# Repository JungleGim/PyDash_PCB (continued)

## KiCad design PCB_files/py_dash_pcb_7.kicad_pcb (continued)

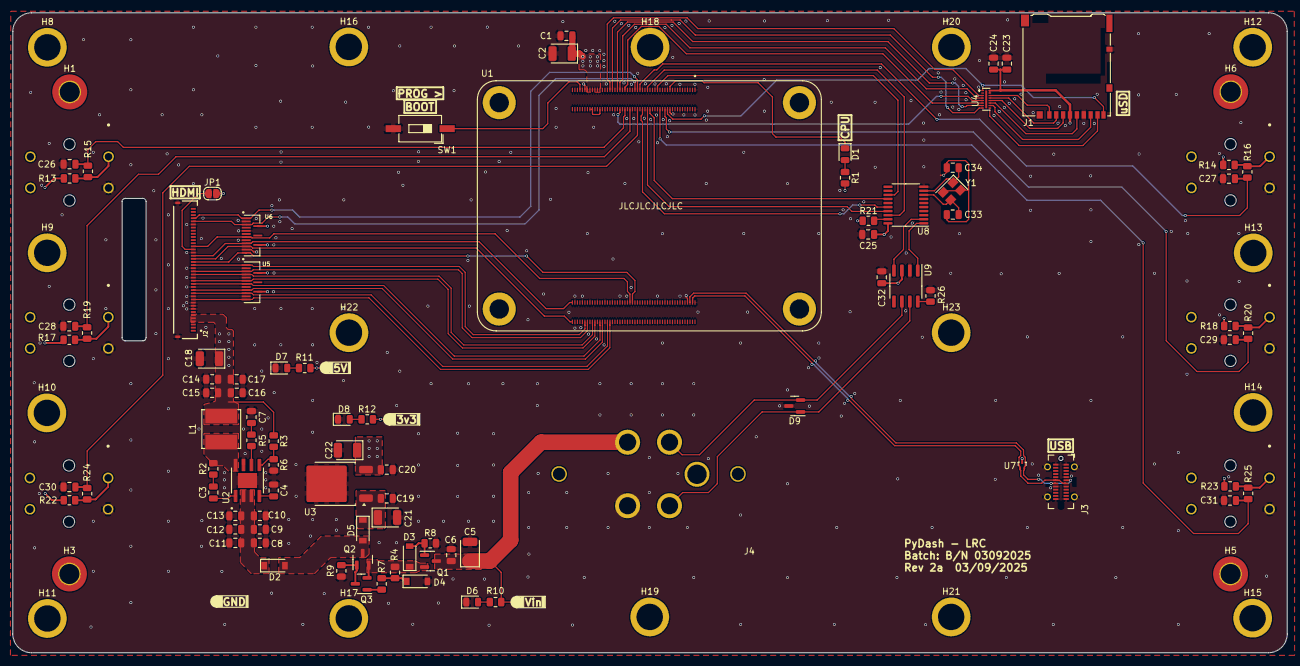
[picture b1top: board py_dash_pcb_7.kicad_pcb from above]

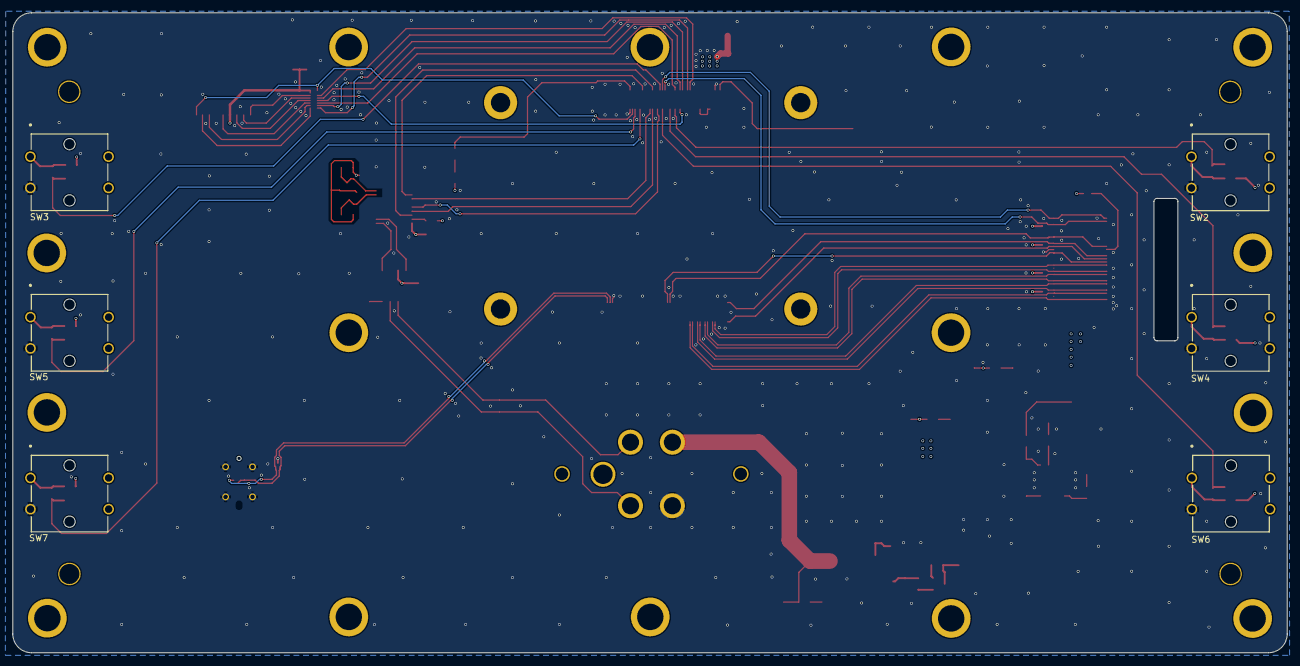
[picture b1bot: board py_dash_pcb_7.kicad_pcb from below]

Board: 4 copper layers, 203.8 x 102.3 mm, 120 parts (6 on the bottom side), 82 nets.

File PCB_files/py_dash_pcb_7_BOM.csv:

"Reference","Value","Qty","Source/Reseller","Reseller_P/N","Footprint","Datasheet","Manufacturer","MPN"
"C1,C6,C19,C20,C26,C27,C28,C29,C30,C31","1u","10","Mouser","80-C0805C105M3R","Capacitor_SMD:C_0805_2012Metric","~","Kemet","C0805C105M3RACTU"
"C2,C5,C21,C22","10u_25v","4","Mouser","80-T495B106K25ATE750","Capacitor_Tantalum_SMD:CP_EIA-3528-21_Kemet-B","~","Kemet","T495B106K025ATE750"
"C3,C4,C23,C25,C32","0u1","5","Mouser","80-C0805C104M5R","Capacitor_SMD:C_0805_2012Metric","~","Kemet","C0805C104M5RACTU"
"C7","1n2","1","Mouser","80-C0805C122K5R","Capacitor_SMD:C_0805_2012Metric","~","Kemet","C0805C122K5RACTU"
"C8,C9,C10,C11,C12,C13,C14,C15,C16,C17,C24","10u","11","Mouser","80-C0805C106K4PAC","Capacitor_SMD:C_0805_2012Metric","~","Kemet","C0805C106K4PAC"
"C18","100u","1","Mouser","581-TPSB107K010R0400","Capacitor_Tantalum_SMD:CP_EIA-3528-21_Kemet-B","293D107X96R3B2TE3","Kyocera","TPSB107K010R0400"
"C33,C34","20p","2","Mouser","80-C0805C200F5G","Capacitor_SMD:C_0805_2012Metric","~","Kemet","C0805C200F5GACTU"
"D1,D6,D7,D8","red","4","Mouser","710-150080RS75000","LED_SMD:LED_0805_2012Metric","~","Wurth","150080RS75000"
"D2,D3,D4,D5","27V","4","Mouser","863-MMSZ27T1G","Diode_SMD:D_SOD-123","~","OnSemi","MMSZ27T1G"
"D9","NUP2105L","1","Mouser","863-NUP2105LT1G","Package_TO_SOT_SMD:SOT-23","http://www.onsemi.com/pub_link/Collateral/NUP2105L-D.PDF","OnSemi","NUP2105LT1G"
"H1,H3,H5,H6","MountingHole_M2","4","N/A","N/A","MountingHole:MountingHole_3.2mm_M3_DIN965_Pad_TopOnly","~","",""
"H2,H4,H7,He1","CM4_M2_1.5ET","4","Mouser","710-9774015243R","MountingHole:MountingHole_3.2mm_M3_DIN965_Pad_TopOnly","~","Wurth","9774015243R"
"H8,H9,H10,H11,H12,H13,H14,H15,H16,H17,H18,H19,H20,H21,H22,H23","Standoff_M2.5_6ET","16","Mouser","153-SMTSO-M25-6ET","user:Standoff_M2.5_6ET","~","PEM","SMTSO-M25-6ET"
"J1","Micro_SD_Card_Det1","1","Mouser","798-DM3ATSFPEJM541 ","Connector_Card:microSD_HC_Hirose_DM3AT-SF-PEJM5","https://datasheet.lcsc.com/lcsc/2110151630_XKB-Connectivity-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","Hirose","DM3AT-SF-PEJM5(41)"
"J2","FFC2B28-40-G","1","Mouser","640-FFC2B28-40-G","user:GCT_FFC2B28-40-G","","GCT","FFC2B28-40-G"
"J3","USB_C_Receptacle_USB2.0_14P","1","Mouser","640-USB4115-03-C ","Connector_USB:USB_C_Receptacle_GCT_USB4115-03-C","https://www.usb.org/sites/default/files/documents/usb_type-c.zip","GCT","USB4115-03-C"
"J4","CANbus","1","Mouser","571-DTP10-4P","user:DT13-4P","~","Deutsch","DTP10-4P"
"J5","CM4-A","1","Mouser","798-DF40C100DS0.4V51","N/A","~","Hirose","DF40C-100DS-0.4V(51)"
"J6","CM4-B","1","Mouser","798-DF40C100DS0.4V51","N/A","~","Hirose","DF40C-100DS-0.4V(51)"
"J7","HDMI_ribbon","1","Mouser","640-540-D0152A4064T","N/A","~","GCT","05-40-D-0152-A-4-06-4-G"
"J8","HDMI_Display","1","Waveshare","70H-1024600-IPS-A","N/A","https://www.waveshare.com/70h-1024600.htm?sku=22671","Waveshare","70H-1024600-IPS-A"
"J9,J10,J11,J12,J13,J14","12x12 keycap - white","6","Mouser","653-B32-1360","N/A","","Omron","B32-1360"
"JP1","p18_jmp","1","N/A","N/A","Jumper:SolderJumper-2_P1.3mm_Open_RoundedPad1.0x1.5mm","~","",""
"L1","3h3","1","Mouser","652-SRN6045-3R3Y","Inductor_SMD:L_Bourns_SRN6045TA","SRN6045TA-3R3Y","Bourns","SRN6045-3R3Y"
"NT1","NetTie_2","1","N/A","N/A","user:NetTie-2_SMD_Pad0.2mm","~","",""
"Q1,Q2,Q3","DMG2307","3","Mouser","621-DMG2307L-7","Package_TO_SOT_SMD:SOT-23","~","Diodes","DMG2307L-7"
"R1,R12","660r","2","Mouser","71-CRCW0805-665-E3 ","Resistor_SMD:R_0805_2012Metric","~","Vishay","CRCW0805665RFKEA"
"R2","10r","1","Mouser","71-CRCW0805-10-E3","Resistor_SMD:R_0805_2012Metric","~","Vishay","CRCW080510R0FKEA"
"R3","12k 1%","1","Mouser","71-CRCW0805-12K","Resistor_SMD:R_0805_2012Metric","~","Vishay","CRCW080512K0FKTA"
"R4,R7,R8,R9,R13,R14,R17,R18,R21,R22,R23","10k","11","Mouser","71-CRCW0805-10K-E3","Resistor_SMD:R_0805_2012Metric","~","Vishay","CRCW080510K0FKEA"
"R5","20k 1%","1","Mouser","71-CRCW0805-20K-E3","Resistor_SMD:R_0805_2012Metric","~","Vishay","CRCW080520K0FKEA"
"R6","2k2 1%","1","Mouser","71-CRCW0805-2.2K-E3","Resistor_SMD:R_0805_2012Metric","~","Vishay","CRCW08052K20FKEA"
"R10","2k7","1","Mouser","71-CRCW0805-2.7K-E3","Resistor_SMD:R_0805_2012Metric","~","Vishay","CRCW08052K70FKEA"
"R11","1k","1","Mouser","71-CRCW0805-1.0K-E3","Resistor_SMD:R_0805_2012Metric","~","Vishay","CRCW08051K00FKEA"
"R15,R16,R19,R20,R24,R25","27k","6","Mouser","71-CRCW0805-27K-E3","Resistor_SMD:R_0805_2012Metric","~","Vishay","CRCW080527K0FKEA"
"R26","4k7","1","Mouser","71-CRCW0805-4.7K-E3","Resistor_SMD:R_0805_2012Metric","~","Vishay","CRCW08054K70FKEA"
"SW1","nBoot","1","Mouser","774-219G-2ESF","Button_Switch_SMD:SW_DIP_SPSTx01_Slide_6.7x4.1mm_W8.61mm_P2.54mm_LowProfile","~","CTS","219G-2ESF"
"SW2,SW3,SW4,SW5,SW6,SW7","SW_Push","6","Mouser","653-B3F-5050","user:SW_B3F-4050_OMR","~","Omron","B3F-5050"
"TP1","TP_3v3","1","N/A","N/A","TestPoint:TestPoint_Pad_D1.0mm","~","",""
"TP2","TP_5V","1","N/A","N/A","TestPoint:TestPoint_Pad_D1.0mm","~","",""
"TP3","TP_12V","1","N/A","N/A","TestPoint:TestPoint_Pad_D1.0mm","~","",""
"TP4","TP_GND","1","N/A","N/A","TestPoint:TestPoint_Pad_D1.0mm","~","",""
"U1","CM4102008","1","Digikey","2648-SC0696-ND","user:MODULE_CM4102008","","Raspberry PI","CM4001008"
"U2","AP64501SP-13","1","Mouser","621-AP64501SP-13","user:SOIC127P600X170-9N","","Diodes","AP64501SP-13"
"U3","BD33FC0FP","1","Mouser","863-NCV1117DT33T5G","Package_TO_SOT_SMD:TO-252-2","https://fscdn.rohm.com/en/products/databook/datasheet/ic/pow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","OnSemi","NCV1117DT33T5G"
"U4","EMIF06-MSD02N16","1","Mouser","511-EMIF06-MSD02N16","user:EMIF06MSD02N16","","ST","EMIF06-MSD02N16"
"U5,U6","TPD8S009DSMR","2","Mouser","595-TPD8S009DSMR","user:IC_TPD8S009DSMR","","TI","TPD8S009DSMR"
"U7","TPD2EUSB30","1","Mouser","595-TPD2E009DRTR","Package_TO_SOT_SMD:Texas_DRT-3","http://www.ti.com/lit/ds/symlink/tpd2eusb30a.pdf","TI","TPD2E009DRTR"
"U8","MCP2515-xST","1","Mouser","579-MCP2515T-E/ST","Package_SO:TSSOP-20_4.4x6.5mm_P0.65mm","http://ww1.microchip.com/downloads/en/DeviceDoc/21801e.pdf","Microchip","MCP2515T-E/ST"
"U9","SN65HVD234","1","Mouser","595-SN65HVD234DR","Package_SO:SOIC-8_3.9x4.9mm_P1.27mm","http://www.ti.com/lit/ds/symlink/sn65hvd234.pdf","TI","SN65HVD234DR"
"Y1","16Mhz","1","Mouser","732-FA-23816B-C3","Crystal:Crystal_SMD_3225-4Pin_3.2x2.5mm","~","Epson","FA-238 16.0000MB-C3"

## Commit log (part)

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2025-05-07 Ref docs upload
2025-05-07 Rev0 render image
2025-05-07 Rev0 PCB files
    Upload initial issue PCB files; TBD some 3d model files in the user lib are too large to web upload
2025-05-22 removed old gerbers
2025-05-22 r1a upload
    uploaded files for r1a; correct button numbering
2025-05-22 r1a readme
2026-02-16 Update README.md
    Added GNU GPLv3
2026-02-16 Rev2a initial upload
    non-PCB files
2026-02-16 Rev2a initial upload
    PCB files
2026-02-16 Rev2a Initial Upload
    ref docs
2026-02-16 Rev2.0a initial upload
    user lib files
2026-02-16 Rev2.0a Initial upload
2026-02-16 Update README.md
    included other PyDash public repositories
2026-03-08 push from desktop to align files
2026-03-08 updated gitignore
2026-03-08 updated readme + relinked proj
    relinked project to work with new folder structure
2026-03-10 resolved tracker TODOs
    Updated USBC placement to work with enclosure. Updated HDMI routes with chosen stackup to meet design requirements. Re-generated PCB fab files.
2026-03-17 final BOM and tweaking
    Tweaked some dimensions after mechanical assembly. Generated BOM and reviewed against reseller inventory
2026-04-04 updated gerbers for rev2.0a testing manufacture order
